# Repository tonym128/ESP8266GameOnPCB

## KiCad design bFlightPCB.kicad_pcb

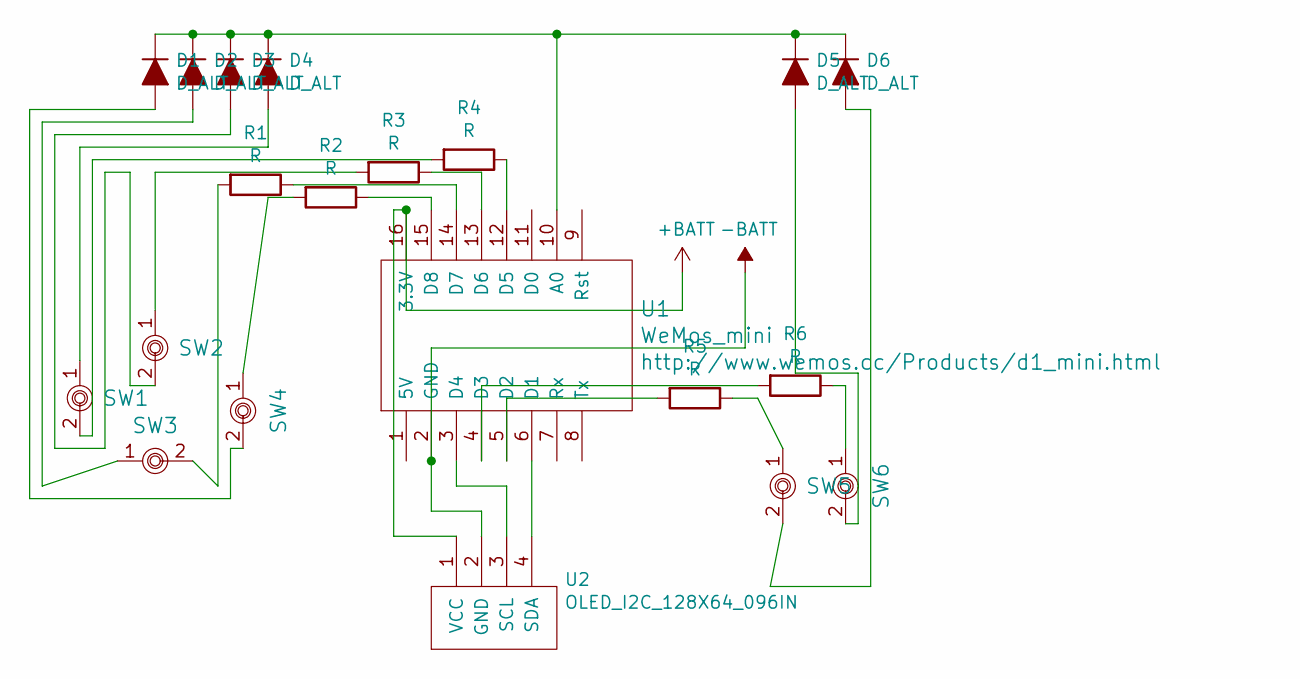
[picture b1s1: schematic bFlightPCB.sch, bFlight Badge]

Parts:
D1, D2, D3, D4, D5, D6: D_ALT; D_DO-35_SOD27_P2.54mm_Vertical_AnodeUp
R1, R2, R3, R4, R5, R6: R; R_Axial_DIN0204_L3.6mm_D1.6mm_P1.90mm_Vertical
SW1, SW2, SW3, SW4, SW5, SW6: ESC_Pad_D
U1: WeMos_mini; D1_mini_board
U2: OLED_I2C_128X64_096IN

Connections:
+BATT: U1.16 (3.3V), U2.1 (VCC)
-BATT: U1.2 (GND), U2.2 (GND)
unnamed: D1.1 (K), D2.1 (K), D3.1 (K), D4.1 (K), D5.1 (K), D6.1 (K), U1.10 (A0)
unnamed: D1.2 (A), SW4.2
unnamed: D2.2 (A), SW3.1
unnamed: D3.2 (A), SW2.2
unnamed: D4.2 (A), SW1.1
unnamed: D5.2 (A), SW6.2
unnamed: D6.2 (A), SW5.2
unnamed: R1.1, U1.14 (D7)
unnamed: R1.2, SW3.2
unnamed: R2.1, U1.15 (D8)
unnamed: R2.2, SW4.1
unnamed: R3.1, U1.13 (D6)
unnamed: R3.2, SW2.1
unnamed: R4.1, U1.12 (D5)
unnamed: R4.2, SW1.2
unnamed: R5.1, SW5.1
unnamed: R5.2, U1.5 (D2)
unnamed: R6.1, SW6.1
unnamed: R6.2, U1.4 (D3)
unnamed: U1.3 (D4), U2.3 (SCL)
unnamed: U1.6 (D1), U2.4 (SDA)

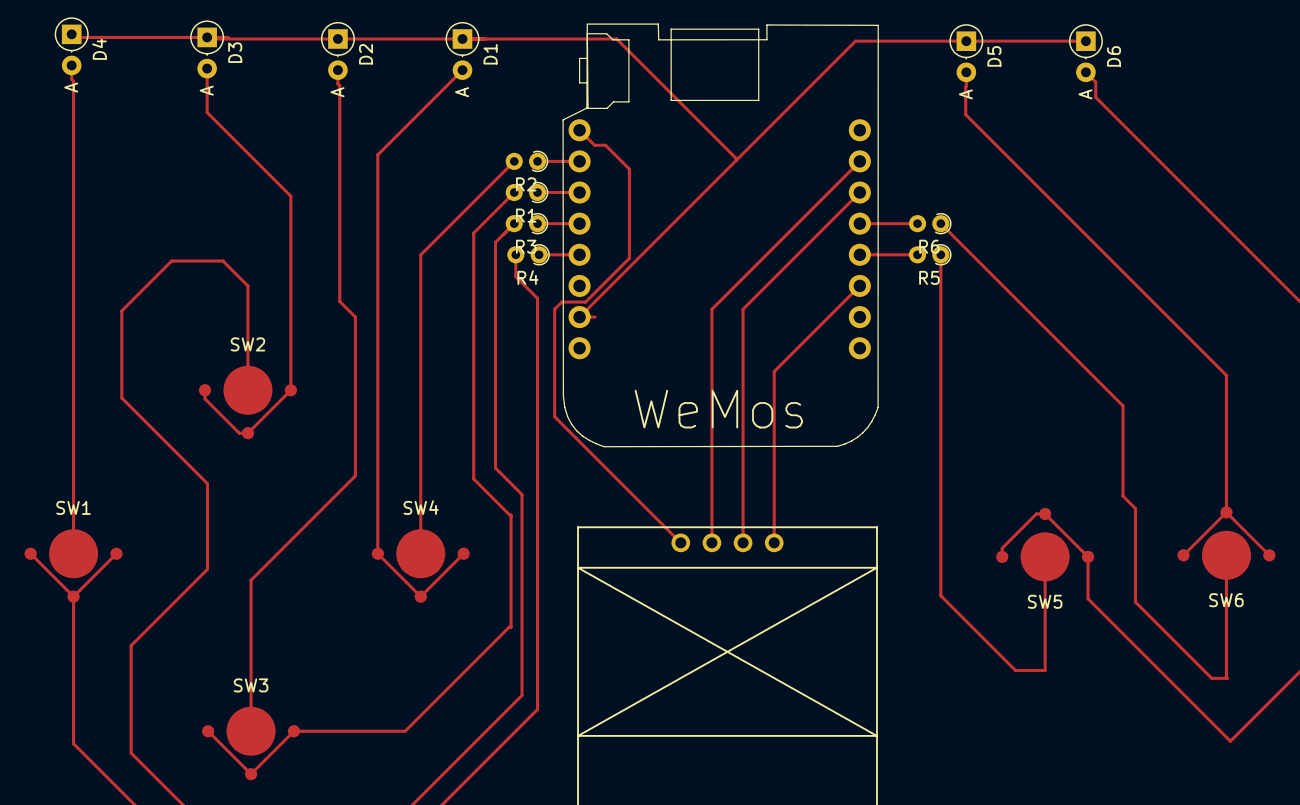
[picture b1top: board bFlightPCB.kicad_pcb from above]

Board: 2 copper layers, 20 parts (0 on the bottom side), 23 nets.

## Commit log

2019-04-24 Updated component on PCB to smaller layout
2019-04-24 Added readme
